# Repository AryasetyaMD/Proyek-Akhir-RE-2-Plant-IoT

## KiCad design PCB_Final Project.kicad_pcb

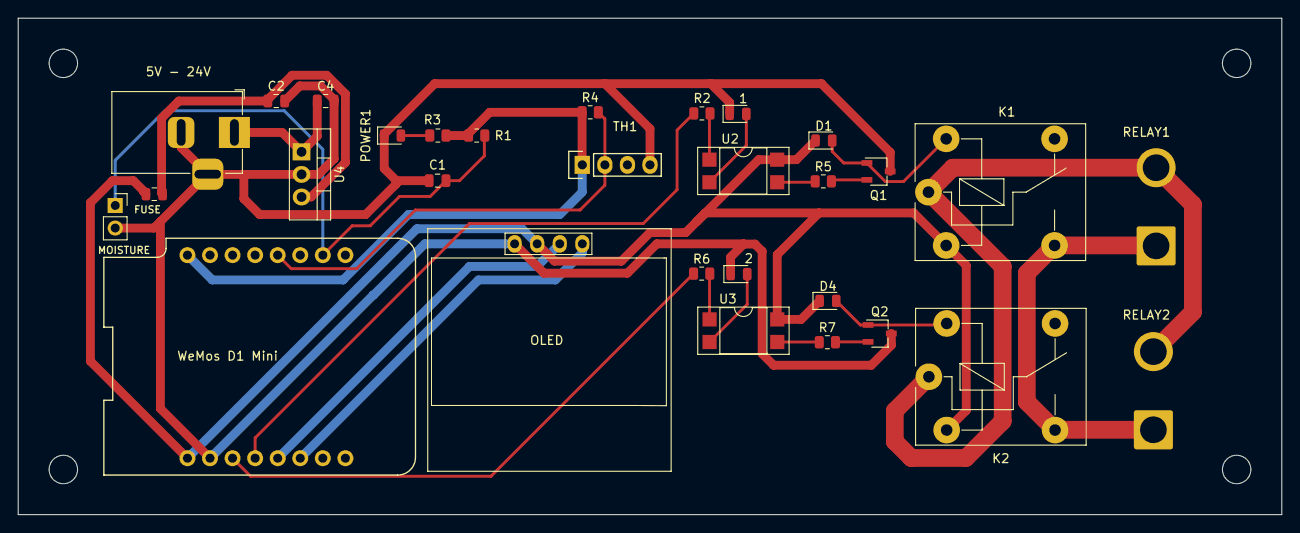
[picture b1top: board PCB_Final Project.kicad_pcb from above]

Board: 2 copper layers, 142.2 x 55.9 mm, 30 parts (0 on the bottom side), 24 nets.

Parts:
1, 2: LED; LED_0805_2012Metric
5V - 24V: Barrel_Jack_Switch; BarrelJack_Horizontal
C1: 0.1uF; C_0805_2012Metric
C2, C4: 0.33uF; C_0805_2012Metric
D1, D4: 1N4007; D_0805_2012Metric
FUSE: Fuse; Fuse_0805_2012Metric
K1, K2: Relay_SPDT; Relay_SPDT_Finder_36.11
MOISTURE: Conn_01x02_Pin; PinSocket_1x02_P2.54mm_Vertical
OLED: SSD1306; 128x64OLED
POWER1: LED; LED_0805_2012Metric
Q1, Q2: NPN; TSOT-23
R1: 10k; R_0805_2012Metric
R2, R6: 330; R_0805_2012Metric
R3: 220; R_0805_2012Metric
R4: 5.1k; R_0805_2012Metric
R5, R7: 1k; R_0805_2012Metric
RELAY1, RELAY2: Conn_01x02_Socket; SolderWire-2.5sqmm_1x02_P8.8mm_D2.4mm_OD4.4mm
TH1: DHT22_Temperature_Humidity
U2, U3: PC817; DIP-4_W7.62mm_SMDSocket_SmallPads
U4: LM7805_TO220; TO-220-3_Vertical
WeMos D1 Mini: WeMos_D1_mini; wemos-d1-mini-with-pin-header

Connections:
/3.3V: R1.1, R3.1, R4.1, TH1.1 (VDD), WeMos D1 Mini.8 (3.3V)
/5V: D1.1 (K), D4.1 (K), FUSE.2, K1.A1, K2.A1, OLED.2 (VCC), U2.4, U3.4, WeMos D1 Mini.9 (5V)
/ANALOG_MOISTURE: C1.1, MOISTURE.1, R1.2, WeMos D1 Mini.2 (A0)
/COM: K1.11, K2.11, RELAY1.2, RELAY2.2
/DHT_DATA: R4.2, TH1.2 (DATA), WeMos D1 Mini.4 (D5)
/IN: R2.1, WeMos D1 Mini.12 (D3)
/IN2: R6.1, WeMos D1 Mini.11 (D4)
/NO: K1.14, K2.14, RELAY1.1, RELAY2.1
/SCL: OLED.3 (SCL), WeMos D1 Mini.13 (D2)
/SDA: OLED.4 (SDA), WeMos D1 Mini.14 (D1)
GND: 1.1 (K), 2.1 (K), 5V - 24V.2, 5V - 24V.3, C1.2, C2.2, C4.2, MOISTURE.2, OLED.1 (GND), POWER1.1 (K), Q1.3 (E), Q2.3 (E), TH1.4 (GND), U4.2 (GND), WeMos D1 Mini.10 (GND)
unnamed: D1.2 (A), K1.A2, Q1.1 (C)
unnamed: 2.2 (A), U3.2
unnamed: 1.2 (A), U2.2
unnamed: D4.2 (A), K2.A2, Q2.1 (C)
unnamed: POWER1.2 (A), R3.2
unnamed: Q1.2 (B), R5.2
unnamed: Q2.2 (B), R7.2
unnamed: R2.2, U2.1
unnamed: R5.1, U2.3
unnamed: R6.2, U3.1
unnamed: R7.1, U3.3
unnamed: 5V - 24V.1, C4.1, U4.1 (VI)
unnamed: C2.1, FUSE.1, U4.3 (VO)

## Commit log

2023-12-12 update schematic
2023-12-12 pcb done
2023-12-12 drc error correction
2023-12-13 update tag pcb
2023-12-13 small correction on pcb
2023-12-14 add alternate power & revamp pcb
2023-12-20 final commit
